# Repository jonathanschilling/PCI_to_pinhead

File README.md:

# PCI_to_pinhead

This is my first KiCad project.
It is an adapter for PCI slot to pin headers.

Here's a view of the prototype:

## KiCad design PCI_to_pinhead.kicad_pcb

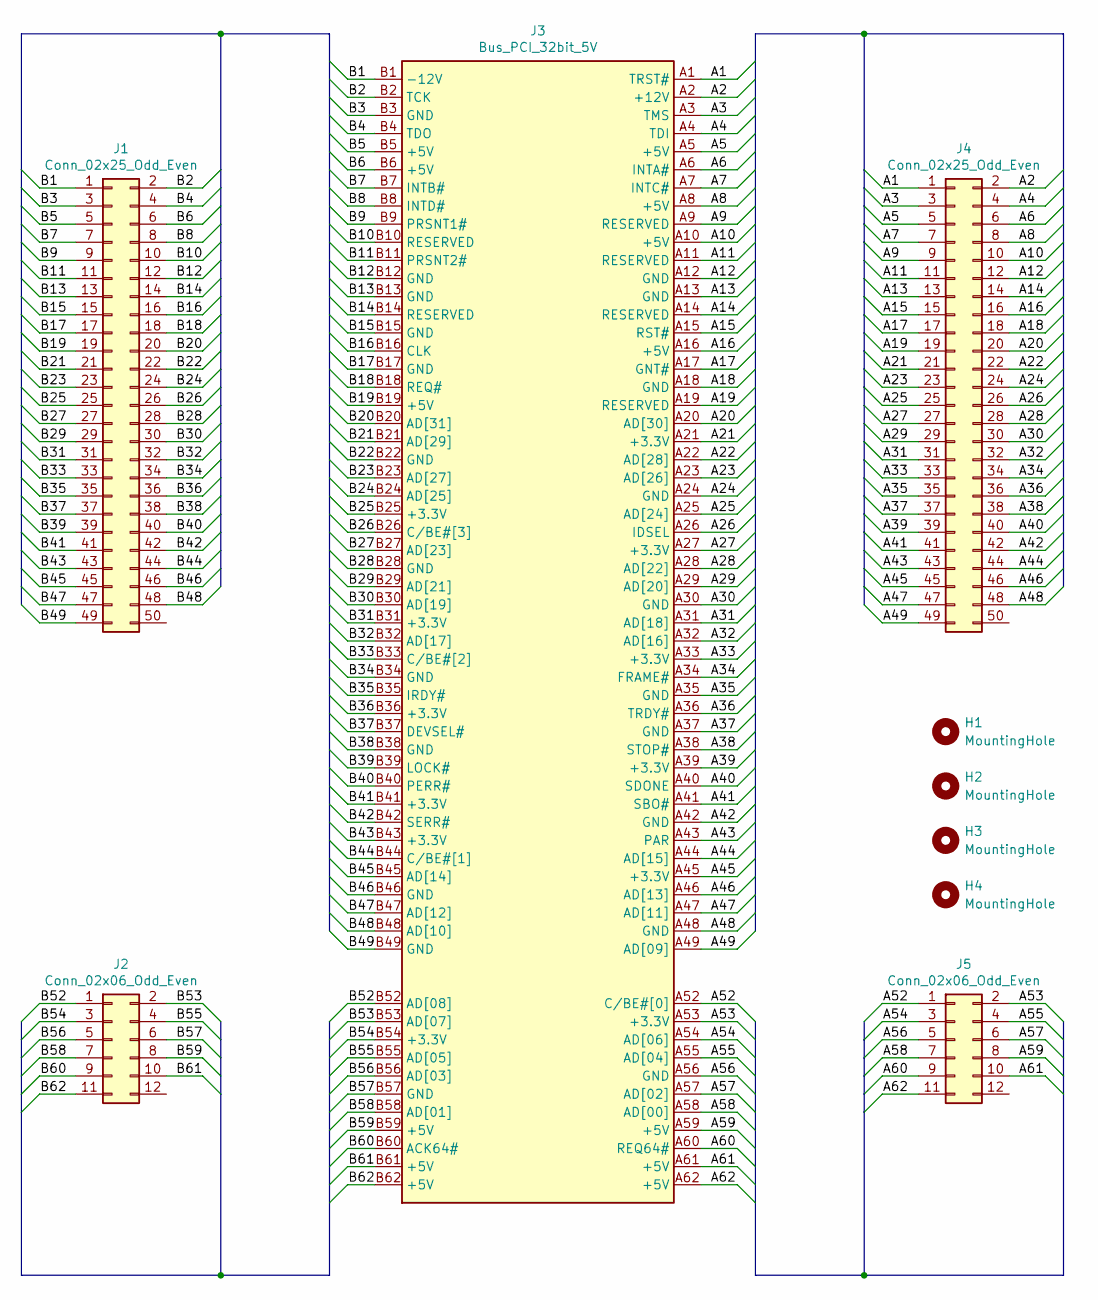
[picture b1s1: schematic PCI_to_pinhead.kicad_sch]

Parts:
H1, H2, H3, H4: MountingHole; MountingHole_3.2mm_M3
J1, J4: Conn_02x25_Odd_Even; PinHeader_2x25_P2.54mm_Vertical
J2, J5: Conn_02x06_Odd_Even; PinHeader_2x06_P2.54mm_Vertical
J3: Bus_PCI_32bit_5V; BUS_PCI_Slot

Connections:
/A1: J3.A1 (TRST#), J4.1
/A2: J3.A2 (+12V), J4.2
/A3: J3.A3 (TMS), J4.3
/A4: J3.A4 (TDI), J4.4
/A5: J3.A5 (+5V), J4.5
/A6: J3.A6 (INTA#), J4.6
/A7: J3.A7 (INTC#), J4.7
/A8: J3.A8 (+5V), J4.8
/A9: J3.A9 (RESERVED), J4.9
/A10: J3.A10 (+5V), J4.10
/A11: J3.A11 (RESERVED), J4.11
/A12: J3.A12 (GND), J4.12
/A13: J3.A13 (GND), J4.13
/A14: J3.A14 (RESERVED), J4.14
/A15: J3.A15 (RST#), J4.15
/A16: J3.A16 (+5V), J4.16
/A17: J3.A17 (GNT#), J4.17
/A18: J3.A18 (GND), J4.18
/A19: J3.A19 (RESERVED), J4.19
/A20: J3.A20 (AD[30]), J4.20
/A21: J3.A21 (+3.3V), J4.21
/A22: J3.A22 (AD[28]), J4.22
/A23: J3.A23 (AD[26]), J4.23
/A24: J3.A24 (GND), J4.24
/A25: J3.A25 (AD[24]), J4.25
/A26: J3.A26 (IDSEL), J4.26
/A27: J3.A27 (+3.3V), J4.27
/A28: J3.A28 (AD[22]), J4.28
/A29: J3.A29 (AD[20]), J4.29
/A30: J3.A30 (GND), J4.30
/A31: J3.A31 (AD[18]), J4.31
/A32: J3.A32 (AD[16]), J4.32
/A33: J3.A33 (+3.3V), J4.33
/A34: J3.A34 (FRAME#), J4.34
/A35: J3.A35 (GND), J4.35
/A36: J3.A36 (TRDY#), J4.36
/A37: J3.A37 (GND), J4.37
/A38: J3.A38 (STOP#), J4.38
/A39: J3.A39 (+3.3V), J4.39
/A40: J3.A40 (SDONE), J4.40
/A41: J3.A41 (SBO#), J4.41
/A42: J3.A42 (GND), J4.42
/A43: J3.A43 (PAR), J4.43
/A44: J3.A44 (AD[15]), J4.44
/A45: J3.A45 (+3.3V), J4.45
/A46: J3.A46 (AD[13]), J4.46
/A47: J3.A47 (AD[11]), J4.47
/A48: J3.A48 (GND), J4.48
/A49: J3.A49 (AD[09]), J4.49
/A52: J3.A52 (C/BE#[0]), J5.1
/A53: J3.A53 (+3.3V), J5.2
/A54: J3.A54 (AD[06]), J5.3
/A55: J3.A55 (AD[04]), J5.4
/A56: J3.A56 (GND), J5.5
/A57: J3.A57 (AD[02]), J5.6
/A58: J3.A58 (AD[00]), J5.7
/A59: J3.A59 (+5V), J5.8
/A60: J3.A60 (REQ64#), J5.9
/A61: J3.A61 (+5V), J5.10
/A62: J3.A62 (+5V), J5.11
/B1: J1.1, J3.B1 (-12V)
/B2: J1.2, J3.B2 (TCK)
/B3: J1.3, J3.B3 (GND)
/B4: J1.4, J3.B4 (TDO)
/B5: J1.5, J3.B5 (+5V)
/B6: J1.6, J3.B6 (+5V)
/B7: J1.7, J3.B7 (INTB#)
/B8: J1.8, J3.B8 (INTD#)
/B9: J1.9, J3.B9 (PRSNT1#)
/B10: J1.10, J3.B10 (RESERVED)
/B11: J1.11, J3.B11 (PRSNT2#)
/B12: J1.12, J3.B12 (GND)
/B13: J1.13, J3.B13 (GND)
/B14: J1.14, J3.B14 (RESERVED)
/B15: J1.15, J3.B15 (GND)
/B16: J1.16, J3.B16 (CLK)
/B17: J1.17, J3.B17 (GND)
/B18: J1.18, J3.B18 (REQ#)
/B19: J1.19, J3.B19 (+5V)
/B20: J1.20, J3.B20 (AD[31])
/B21: J1.21, J3.B21 (AD[29])
/B22: J1.22, J3.B22 (GND)
/B23: J1.23, J3.B23 (AD[27])
/B24: J1.24, J3.B24 (AD[25])
/B25: J1.25, J3.B25 (+3.3V)
/B26: J1.26, J3.B26 (C/BE#[3])
/B27: J1.27, J3.B27 (AD[23])
/B28: J1.28, J3.B28 (GND)
/B29: J1.29, J3.B29 (AD[21])
/B30: J1.30, J3.B30 (AD[19])
/B31: J1.31, J3.B31 (+3.3V)
/B32: J1.32, J3.B32 (AD[17])
/B33: J1.33, J3.B33 (C/BE#[2])
/B34: J1.34, J3.B34 (GND)
/B35: J1.35, J3.B35 (IRDY#)
/B36: J1.36, J3.B36 (+3.3V)
/B37: J1.37, J3.B37 (DEVSEL#)
/B38: J1.38, J3.B38 (GND)
/B39: J1.39, J3.B39 (LOCK#)
/B40: J1.40, J3.B40 (PERR#)
/B41: J1.41, J3.B41 (+3.3V)
/B42: J1.42, J3.B42 (SERR#)
/B43: J1.43, J3.B43 (+3.3V)
/B44: J1.44, J3.B44 (C/BE#[1])
/B45: J1.45, J3.B45 (AD[14])
/B46: J1.46, J3.B46 (GND)
/B47: J1.47, J3.B47 (AD[12])
/B48: J1.48, J3.B48 (AD[10])
/B49: J1.49, J3.B49 (GND)
/B52: J2.1, J3.B52 (AD[08])
/B53: J2.2, J3.B53 (AD[07])
/B54: J2.3, J3.B54 (+3.3V)
/B55: J2.4, J3.B55 (AD[05])
/B56: J2.5, J3.B56 (AD[03])
/B57: J2.6, J3.B57 (GND)
/B58: J2.7, J3.B58 (AD[01])
/B59: J2.8, J3.B59 (+5V)
/B60: J2.9, J3.B60 (ACK64#)
/B61: J2.10, J3.B61 (+5V)
/B62: J2.11, J3.B62 (+5V)

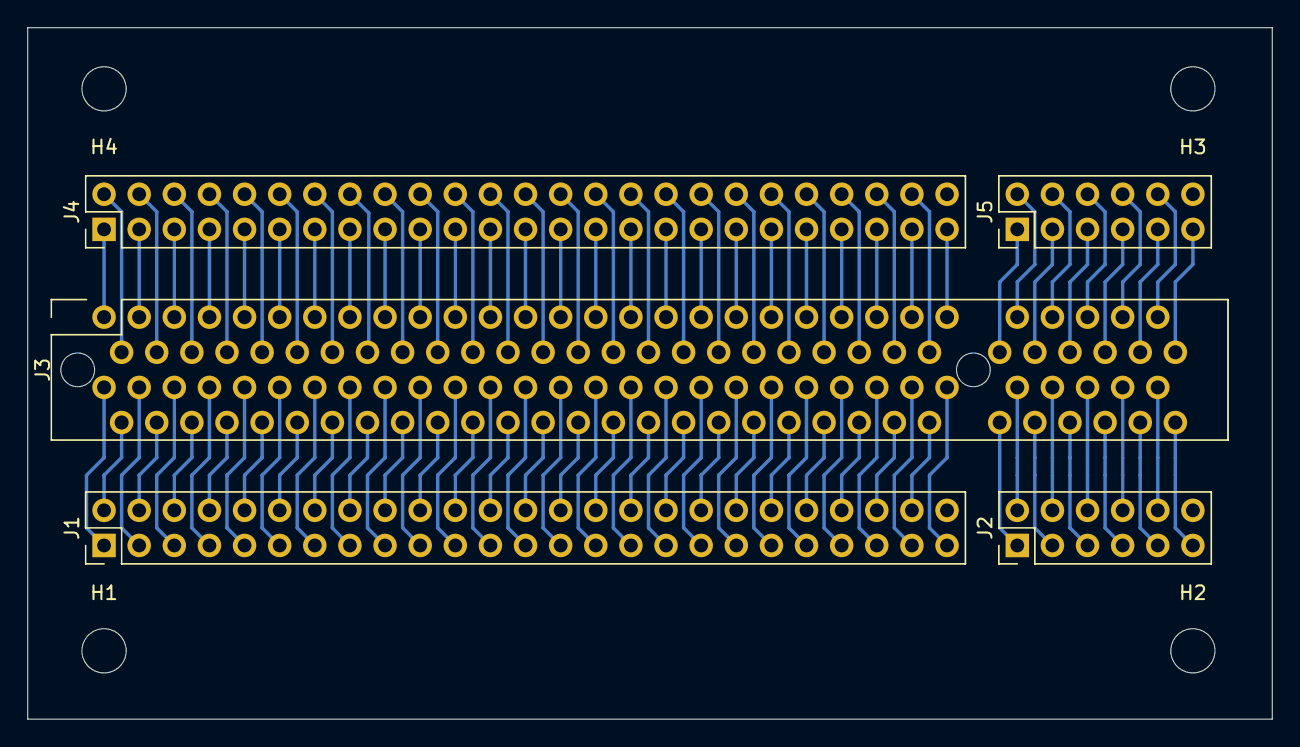
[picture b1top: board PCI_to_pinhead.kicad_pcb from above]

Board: 2 copper layers, 90.0 x 50.0 mm, 9 parts (0 on the bottom side), 120 nets.

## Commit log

2022-06-23 KiCAD 6, added holes to PCI slot and fixed pad size and hole diameters
2022-07-13 first attempt to order from PCBway
2022-09-22 pic of prototype; new backup
